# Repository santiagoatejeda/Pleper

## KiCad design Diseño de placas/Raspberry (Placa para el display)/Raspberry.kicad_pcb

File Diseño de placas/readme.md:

# Carpeta: Diseño de Placas

> Módulos electrónicos del proyecto

---

## Contenido
- `Banco de capacitores/` → Conjunto de capacitores conectados en paralelo para almacenamiento de energía.  
- `Diseño 3D/` → Modelado tridimensional del banco de capacitores y disposición general.  
- `Placa rectificadora/` → Conversión de corriente alterna a continua para carga estable en la batería.
- `Raspberry (Placa para el display)` → Mostrar la tensión generada y crear una página para mostrarla.  
- `Segunda placa rectificadora` → Conversión de corriente alterna a continua para carga estable; placa para la segunda baldosa.
  
---

## Descripción
En esta carpeta se encuentran los **diseños electrónicos** fundamentales del sistema:  
- Implementación de **etapas de rectificación y almacenamiento**.  
- Integración entre módulos para alimentar el sistema de medición y visualización.  

---

## Herramientas utilizadas
- **KiCad** para diseño de PCBs.  
- **PDFGear** para visualización e impresión.
---

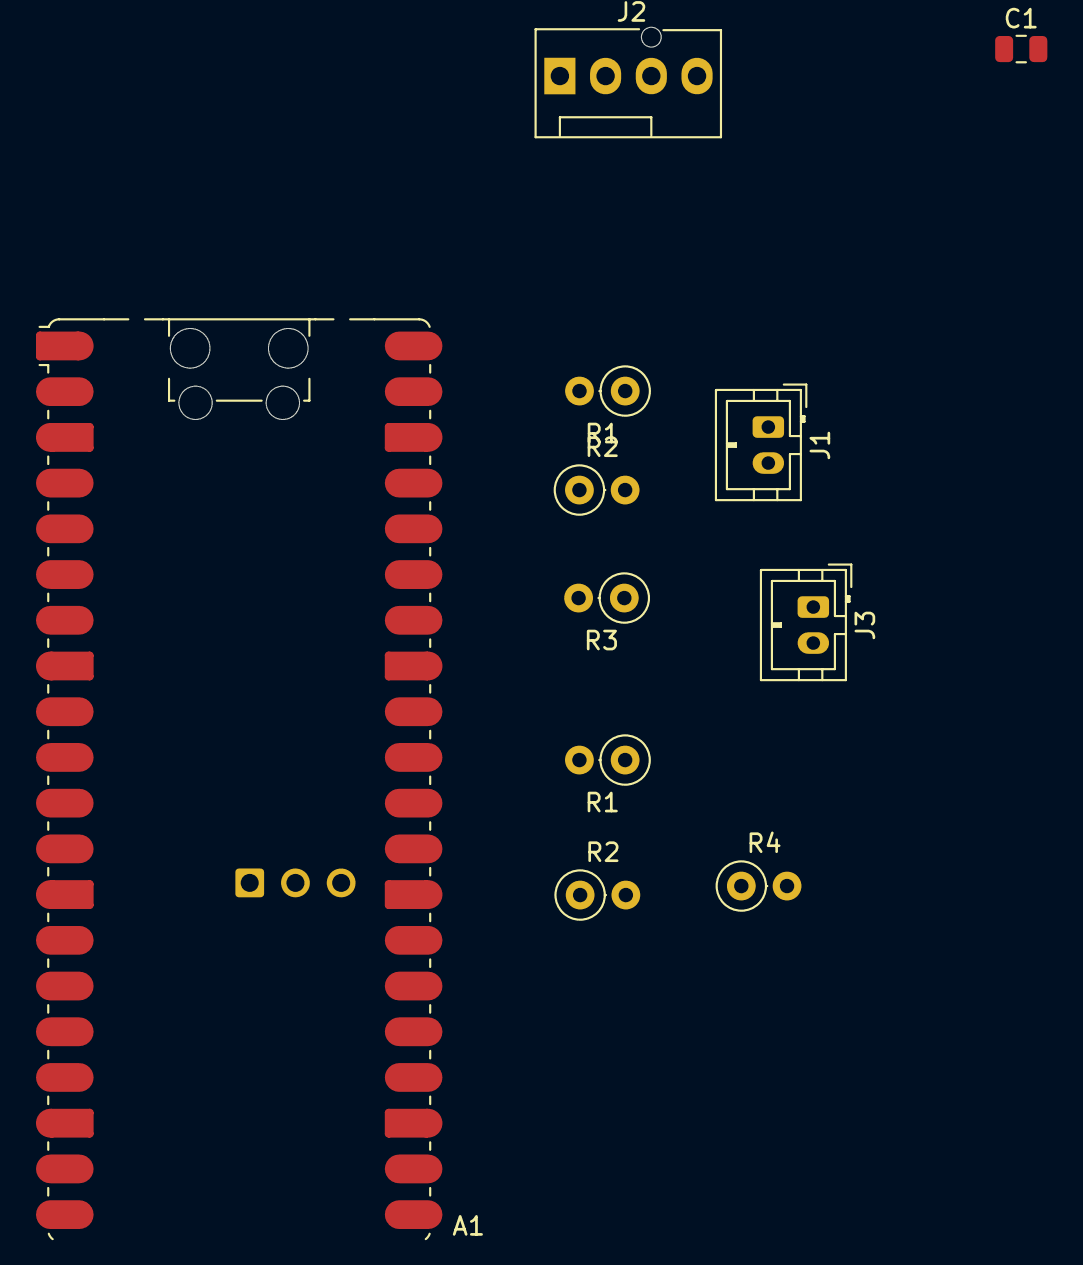
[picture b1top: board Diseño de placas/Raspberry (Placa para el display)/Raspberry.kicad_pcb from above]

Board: 2 copper layers, 11 parts (0 on the bottom side), 8 nets.

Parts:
A1: RaspberryPi_Pico_W; RaspberryPi_Pico_W_SMD_HandSolder
C1: 100nF; C_0805_2012Metric
J1, J3: Conn_01x02_Pin; JST_PH_B2B-PH-K_1x02_P2.00mm_Vertical
J2: Conn_01x04; FanPinHeader_1x04_P2.54mm_Vertical
R1, R2, R2#2, R4: 10K; R_Axial_DIN0207_L6.3mm_D2.5mm_P2.54mm_Vertical
R1#2, R3: 22K; R_Axial_DIN0207_L6.3mm_D2.5mm_P2.54mm_Vertical

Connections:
+3.3V: C1.1, J2.3
ADC0: A1.31 (GPIO26_ADC0), R1#2.2, R2#2.1
ADC1: A1.32 (GPIO27_ADC1), R1.2, R2.1, R3.2, R4.1
Earth: A1.3 (GND), A1.8 (GND), A1.13 (GND), A1.18 (GND), A1.23 (GND), A1.28 (GND), A1.38 (GND), C1.2, J1.2, J2.4, R2.2, R2#2.2, R4.2
GP6: A1.9 (GPIO6), J2.2
GP7: A1.10 (GPIO7), J2.1
J1: J1.1, R1.1
J3 (1): R1#2.1, R3.1

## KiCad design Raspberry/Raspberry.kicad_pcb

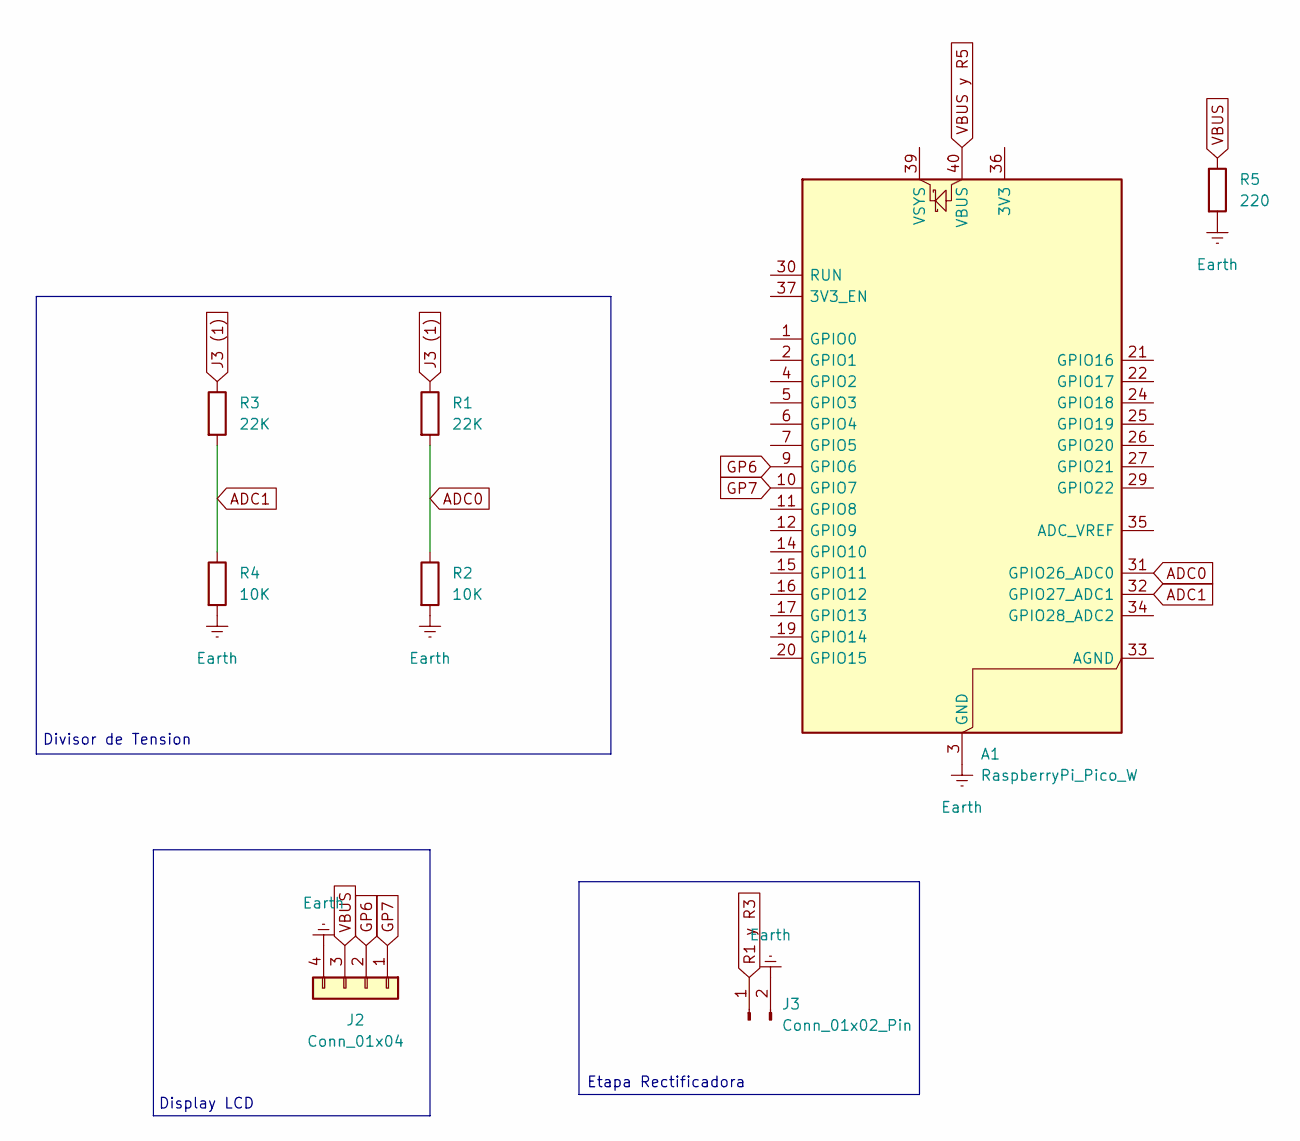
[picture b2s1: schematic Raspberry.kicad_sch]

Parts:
A1: RaspberryPi_Pico_W; RaspberryPi_Pico_W_SMD_HandSolder
J2: Conn_01x04; FanPinHeader_1x04_P2.54mm_Vertical
J3: Conn_01x02_Pin; JST_PH_B2B-PH-K_1x02_P2.00mm_Vertical
R1, R3: 22K; R_Axial_DIN0207_L6.3mm_D2.5mm_P2.54mm_Vertical
R2, R4: 10K; R_Axial_DIN0207_L6.3mm_D2.5mm_P2.54mm_Vertical
R5: 220; R_Axial_DIN0207_L6.3mm_D2.5mm_P2.54mm_Vertical

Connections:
ADC0: A1.31 (GPIO26_ADC0), R1.2, R2.1
ADC1: A1.32 (GPIO27_ADC1), R3.2, R4.1
Earth: A1.3 (GND), A1.8 (GND), A1.13 (GND), A1.18 (GND), A1.23 (GND), A1.28 (GND), A1.38 (GND), J2.4, J3.2, R2.2, R4.2, R5.2
GP6: A1.9 (GPIO6), J2.2
GP7: A1.10 (GPIO7), J2.1
J3 (1): R1.1, R3.1
R1 y R3: J3.1
VBUS: J2.3, R5.1
VBUS y R5: A1.40 (VBUS)

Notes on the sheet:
Divisor de Tension
Display LCD
Etapa Rectificadora

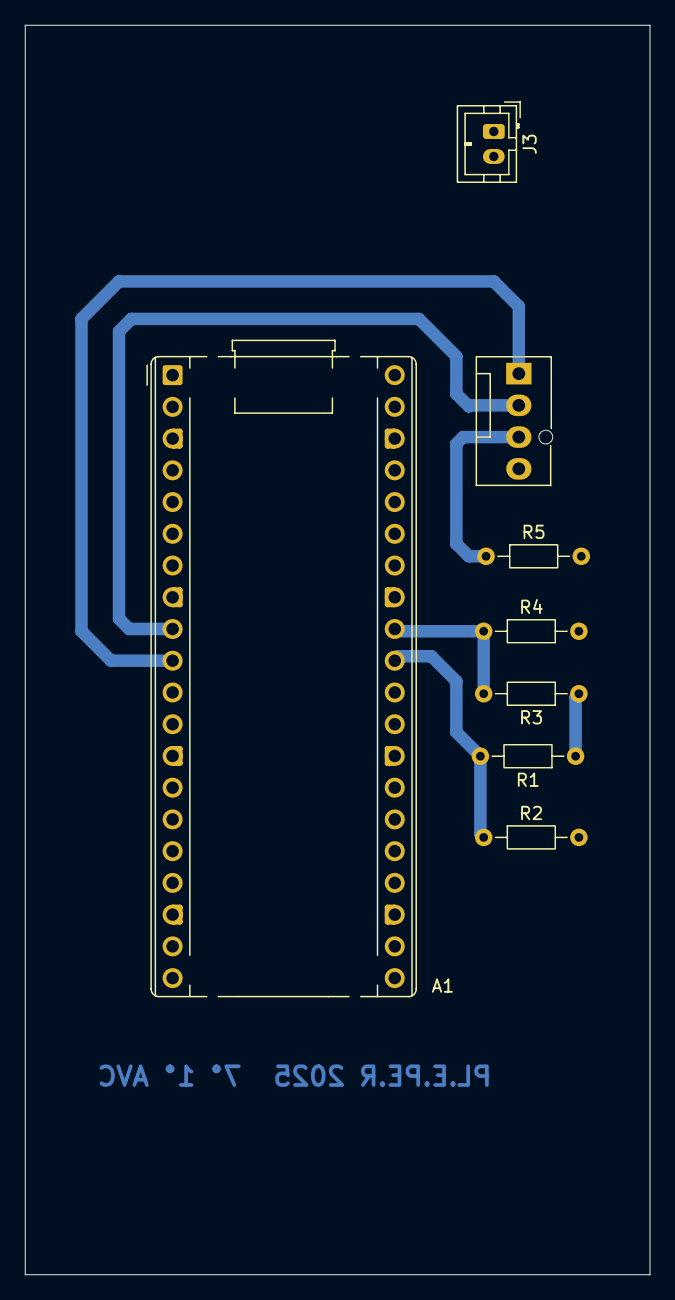
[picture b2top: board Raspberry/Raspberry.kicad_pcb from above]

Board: 2 copper layers, 50.0 x 100.0 mm, 8 parts (0 on the bottom side), 7 nets.

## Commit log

2025-04-08 🕒◽ Updated with Glitch
2025-11-16 codigo completo .c
    .
2025-11-16 correccion del .c
    .
2025-11-16 inclucion de libreria LCD
    .
2025-11-16 carpeta build del .c
    .
2025-11-16 Add progress update for Ignacio Garcia Louzan
2025-11-16 Document progress on server integration with Raspberry Pi
    Added updates on the server integration and issues faced during development.
2025-11-16 Document progress on PLEPER web interface design
    Added details about web interface design for PLEPER.
2025-11-16 Corrige errores y mejora redacción en Agosto.md
    Se corrigieron errores tipográficos y se mejoró la redacción de las contribuciones de los miembros del equipo.
2025-11-16 Update September.md with project progress notes
    Added details about research on TP4056 modules and their functionality.
2025-11-16 Actualización de la PCB, carpeta de campo
2025-11-16 Add entry for Ignacio Garcia Louzan's work
    Added a new entry for Ignacio Garcia Louzan regarding the design of the circuit box and emergency sign placement.
2025-11-16 Revisión de requisitos de cierre
2025-11-16 Organizo la documentación y archivos en sus correspondientes carpetas
2025-11-16 Ordeno las carpetas de código
    COMMIT N°500 VAMOSSSSSSSSSSSSSSSSSSSSSSSSSSSSSSSSSSSSSSSSSSSSSSSSSSSSSSSSSSSSSSSSSSSSSSSSSSSSSSSSSSSSSSSSSSSSSSSSSSSSSSSSSSSSSSSSSSSSSSSSSSSS
2025-11-16 Añado Licencia MIT al proyecto
    Un poco también para investigar y descubrir las cosas que se pueden hacer con GitHub
2025-11-16 Actualizo readme
2025-11-16 Actualizo readme
    Removed main document listings and updated tools used.
2025-11-16 Actualizo el avance en los requisitos de cierre
2025-11-16 Subo Curriculum Vitae
2025-11-17 Cortando tubo de PVC
2025-11-17 Cortando soportes para la estructura
2025-11-17 Subo CV
2025-11-17 lijado de topes 3d
2025-11-17 Perforar la baldosa de madera
2025-11-17 Perforar placa de caucho
2025-11-17 Unir la placa de madera y caucho para la 2da placa
2025-11-17 delete pico sch y pcb
    .
2025-11-17 nuevo sch para la pico
    .
2025-11-17 Reacomodo el cv
2025-11-17 Actualizo cambios en requisitos de cierre y manual de usuario
2025-11-17 Actualizo mi CV
2025-11-17 actualizacion de los elementos de alcance inconclusos
    ,
2025-11-17 Actualizo requisitos de cierre
2025-11-17 Actualizo bitacora septiembre.md
2025-11-17 Pinte los bordes de la primera baldosa con aerosol
2025-11-17 Cortando bases de goma eva de la segunda baldosa
2025-11-17 Pintar caja del display
2025-11-17 Creacion de carpeta de presentaciones pleper
2025-11-17 Presentacion de pleper para la muestra
2025-11-17 Presentacion avances primer cuatrimestre
